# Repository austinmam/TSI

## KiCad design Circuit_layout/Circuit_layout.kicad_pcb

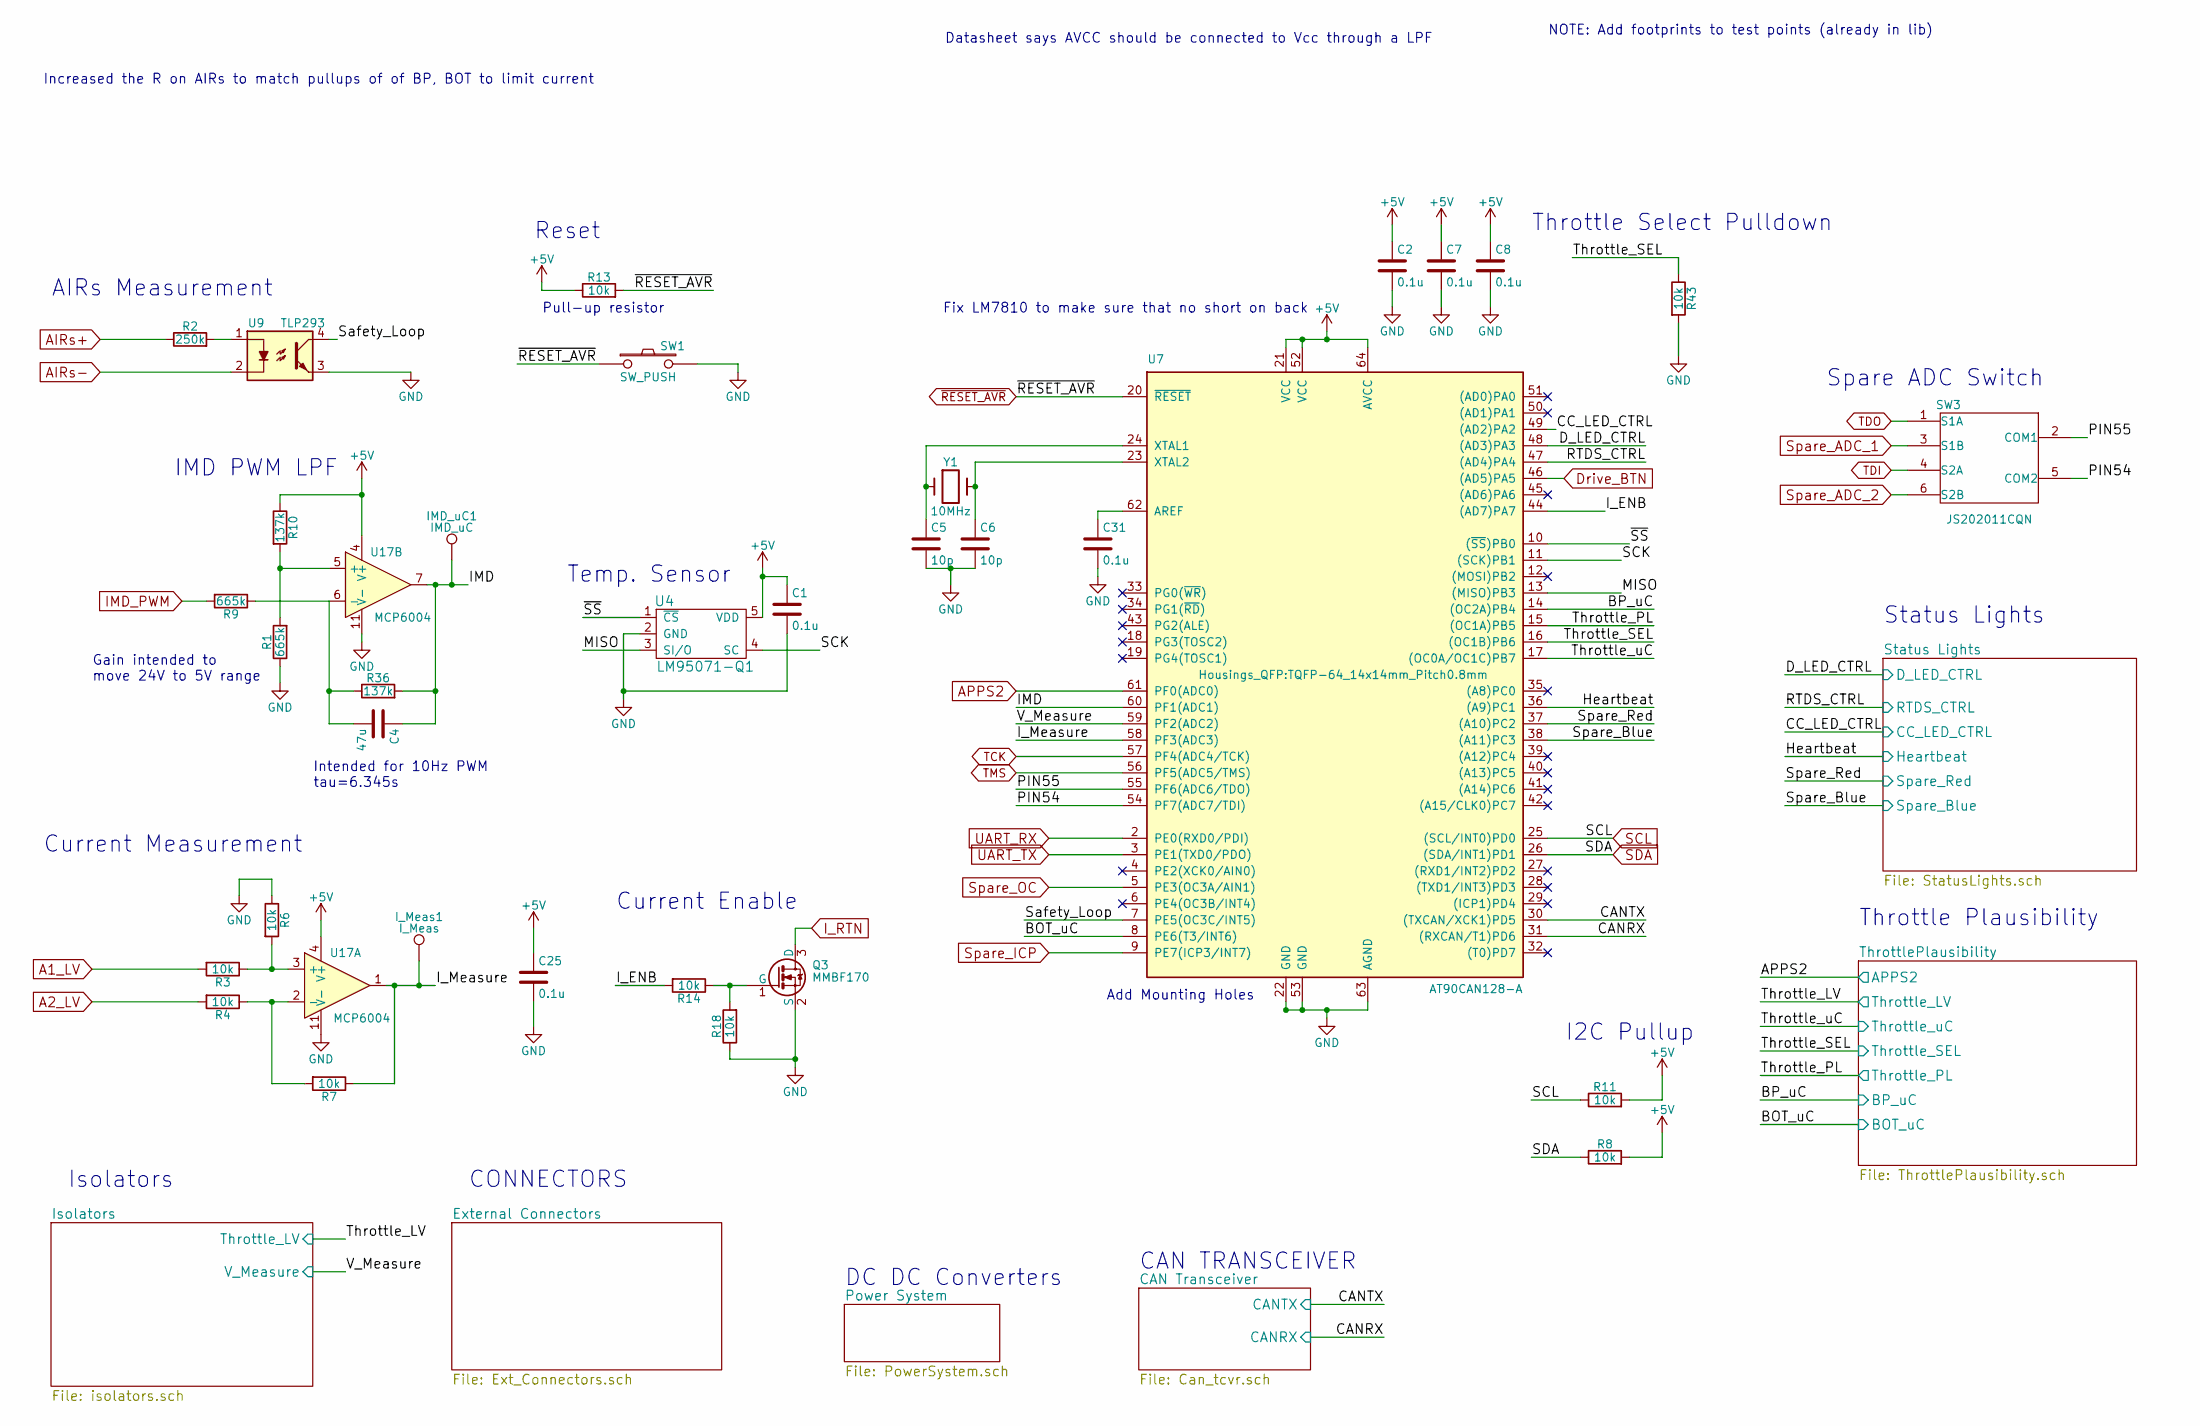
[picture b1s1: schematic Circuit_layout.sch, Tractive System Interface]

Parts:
C1, C2, C7, C8, C25, C31: 0.1u; C_0805_HandSoldering; Digikey P/N 399-1168-1-ND
C4: 47u; C_1210_HandSoldering; Digikey P/N 490-6538-1-ND
C5, C6: 10p; C_0805_HandSoldering; DigiKey P/N 399-1108-1-ND
IMD_uC1: IMD_uC; Measurement_Point_Round-SMD-Pad_Big
I_Meas1: I_Meas; Measurement_Point_Round-SMD-Pad_Big
Q3: MMBF170; SOT-23; Digikey P/N MMBF170CT-ND
R1, R9: 665k; R_0805_HandSoldering; DigiKey P/N P665KCCT-ND
R2: 250k; R_0805_HandSoldering; DigiKey P/N P249KCCT-ND
R3, R4, R6, R7, R8, R11, R13, R14, R18, R43: 10k; R_0805_HandSoldering; DigiKey P/N P10.0KCCT-ND
R10, R36: 137k; R_0805_HandSoldering; DigiKey P/N P137KCCT-ND
SW1: SW_PUSH; SW_RACON_8; DigiKey P/N 1715-1676-1-ND
SW3: JS202011CQN; CK_DPDT_Switch; DigiKey P/N 401-2001-ND
U4: LM95071-Q1; SOT-23-5_HandSoldering; DigiKey P/N 296-40259-1-ND
U7: AT90CAN128-A; TQFP-64_14x14mm_Pitch0.8mm; DigiKey P/N AT90CAN128-16AURCT-ND
U9: TLP293; SOP-4_4.4x2.8mm_Pitch1.27mm; DigiKey P/N TLP293(GB-TPLECT-ND
U17: MCP6004; SOIC-14_3.9x8.7mm_Pitch1.27mm; Digikey P/N MCP6004T-I/SLCT-ND
Y1: 10MHz; crystal_TXC_7A; DigiKey P/N 887-1741-1-ND

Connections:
+5V: C1.1, C2.1, C7.1, C8.1, C25.1, R8.2, R10.1, R11.2, R13.1, U4.5 (VDD), U7.21 (VCC), U7.52 (VCC), U7.64 (AVCC), U17.4 (V+); also elsewhere on the board
/CAN Transceiver/CANRX: U7.31 ((RXCAN/T1)PD6); also elsewhere on the board
/CAN Transceiver/CANTX: U7.30 ((TXCAN/XCK1)PD5); also elsewhere on the board
/IMD: C4.1, IMD_uC1.1, R36.2, U7.60 (PF1(ADC1)), U17.7
/I_ENB: R14.2, U7.44 ((AD7)PA7)
/I_Measure: I_Meas1.1, R7.1, U7.58 (PF3(ADC3)), U17.1
/Isolators/V_Measure: U7.59 (PF2(ADC2)); also elsewhere on the board
/MISO: U4.3 (SI/O), U7.13 ((MISO)PB3)
/PIN54: SW3.5 (COM2), U7.54 (PF7(ADC7/TDI))
/PIN55: SW3.2 (COM1), U7.55 (PF6(ADC6/TDO))
/SCK: U4.4 (SC), U7.11 ((SCK)PB1)
/Safety_Loop: U7.7 (PE5(OC3C/INT5)), U9.4
/Status Lights/CC_LED_CTRL: U7.49 ((AD2)PA2); also elsewhere on the board
/Status Lights/D_LED_CTRL: U7.48 ((AD3)PA3); also elsewhere on the board
/Status Lights/Heartbeat: U7.36 ((A9)PC1); also elsewhere on the board
/Status Lights/RTDS_CTRL: U7.47 ((AD4)PA4); also elsewhere on the board
/Status Lights/Spare_Blue: U7.38 ((A11)PC3); also elsewhere on the board
/Status Lights/Spare_Red: U7.37 ((A10)PC2); also elsewhere on the board
/ThrottlePlausibility/BOT_uC: U7.8 (PE6(T3/INT6)); also elsewhere on the board
/ThrottlePlausibility/BP_uC: U7.14 ((OC2A)PB4); also elsewhere on the board
/ThrottlePlausibility/Throttle_PL: U7.15 ((OC1A)PB5); also elsewhere on the board
/ThrottlePlausibility/Throttle_SEL: R43.1, U7.16 ((OC1B)PB6); also elsewhere on the board
/ThrottlePlausibility/Throttle_uC: U7.17 ((OC0A/OC1C)PB7); also elsewhere on the board
/~SS: U4.1 (~CS), U7.10 ((~SS~)PB0)
A1_LV: R3.2; also elsewhere on the board
A2_LV: R4.2; also elsewhere on the board
AIRs+: R2.1; also elsewhere on the board
AIRs-: U9.2; also elsewhere on the board
APPS2: U7.61 (PF0(ADC0)); also elsewhere on the board
Drive_BTN: U7.46 ((AD5)PA5); also elsewhere on the board
IMD_PWM: R9.2; also elsewhere on the board
I_RTN: Q3.3 (D); also elsewhere on the board
unnamed: C4.2, R9.1, R36.1, U17.6 (-)
unnamed: C5.1, U7.24 (XTAL1), Y1.1
unnamed: C6.1, U7.23 (XTAL2), Y1.2
unnamed: C31.1, U7.62 (AREF)
unnamed: Q3.1 (G), R14.1, R18.2
unnamed: R1.2, R10.2, U17.5 (+)
unnamed: R2.2, U9.1
unnamed: R3.1, R6.2, U17.3 (+)
unnamed: R4.1, R7.2, U17.2 (-)
SCL: R11.1, U7.25 ((SCL/INT0)PD0); also elsewhere on the board
SDA: R8.1, U7.26 ((SDA/INT1)PD1); also elsewhere on the board
Spare_ADC_1: SW3.3 (S1B); also elsewhere on the board
Spare_ADC_2: SW3.6 (S2B); also elsewhere on the board
Spare_ICP: U7.9 (PE7(ICP3/INT7)); also elsewhere on the board
Spare_OC: U7.5 (PE3(OC3A/AIN1)); also elsewhere on the board
TCK: U7.57 (PF4(ADC4/TCK)); also elsewhere on the board
TDI: SW3.4 (S2A); also elsewhere on the board
TDO: SW3.1 (S1A); also elsewhere on the board
TMS: U7.56 (PF5(ADC5/TMS)); also elsewhere on the board
UART_RX: U7.2 (PE0(RXD0/PDI)); also elsewhere on the board
UART_TX: U7.3 (PE1(TXD0/PDO)); also elsewhere on the board
~RESET_AVR: R13.2, SW1.1, U7.20 (~RESET); also elsewhere on the board

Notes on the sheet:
CONNECTORS
CAN TRANSCEIVER
Current Measurement
IMD PWM LPF
AIRs Measurement
Throttle Plausibility
Status Lights
DC DC Converters
Isolators
Add Mounting Holes
Intended for 10Hz PWM tau=6.345s
I2C Pullup
Datasheet says AVCC should be connected to Vcc through a LPF
Pull-up resistor
Reset
Throttle Select Pulldown
NOTE: Add footprints to test points (already in lib)
Spare ADC Switch
Increased the R on AIRs to match pullups of of BP, BOT to limit current
Current Enable
Gain intended to move 24V to 5V range
Temp. Sensor
Fix LM7810 to make sure that no short on back

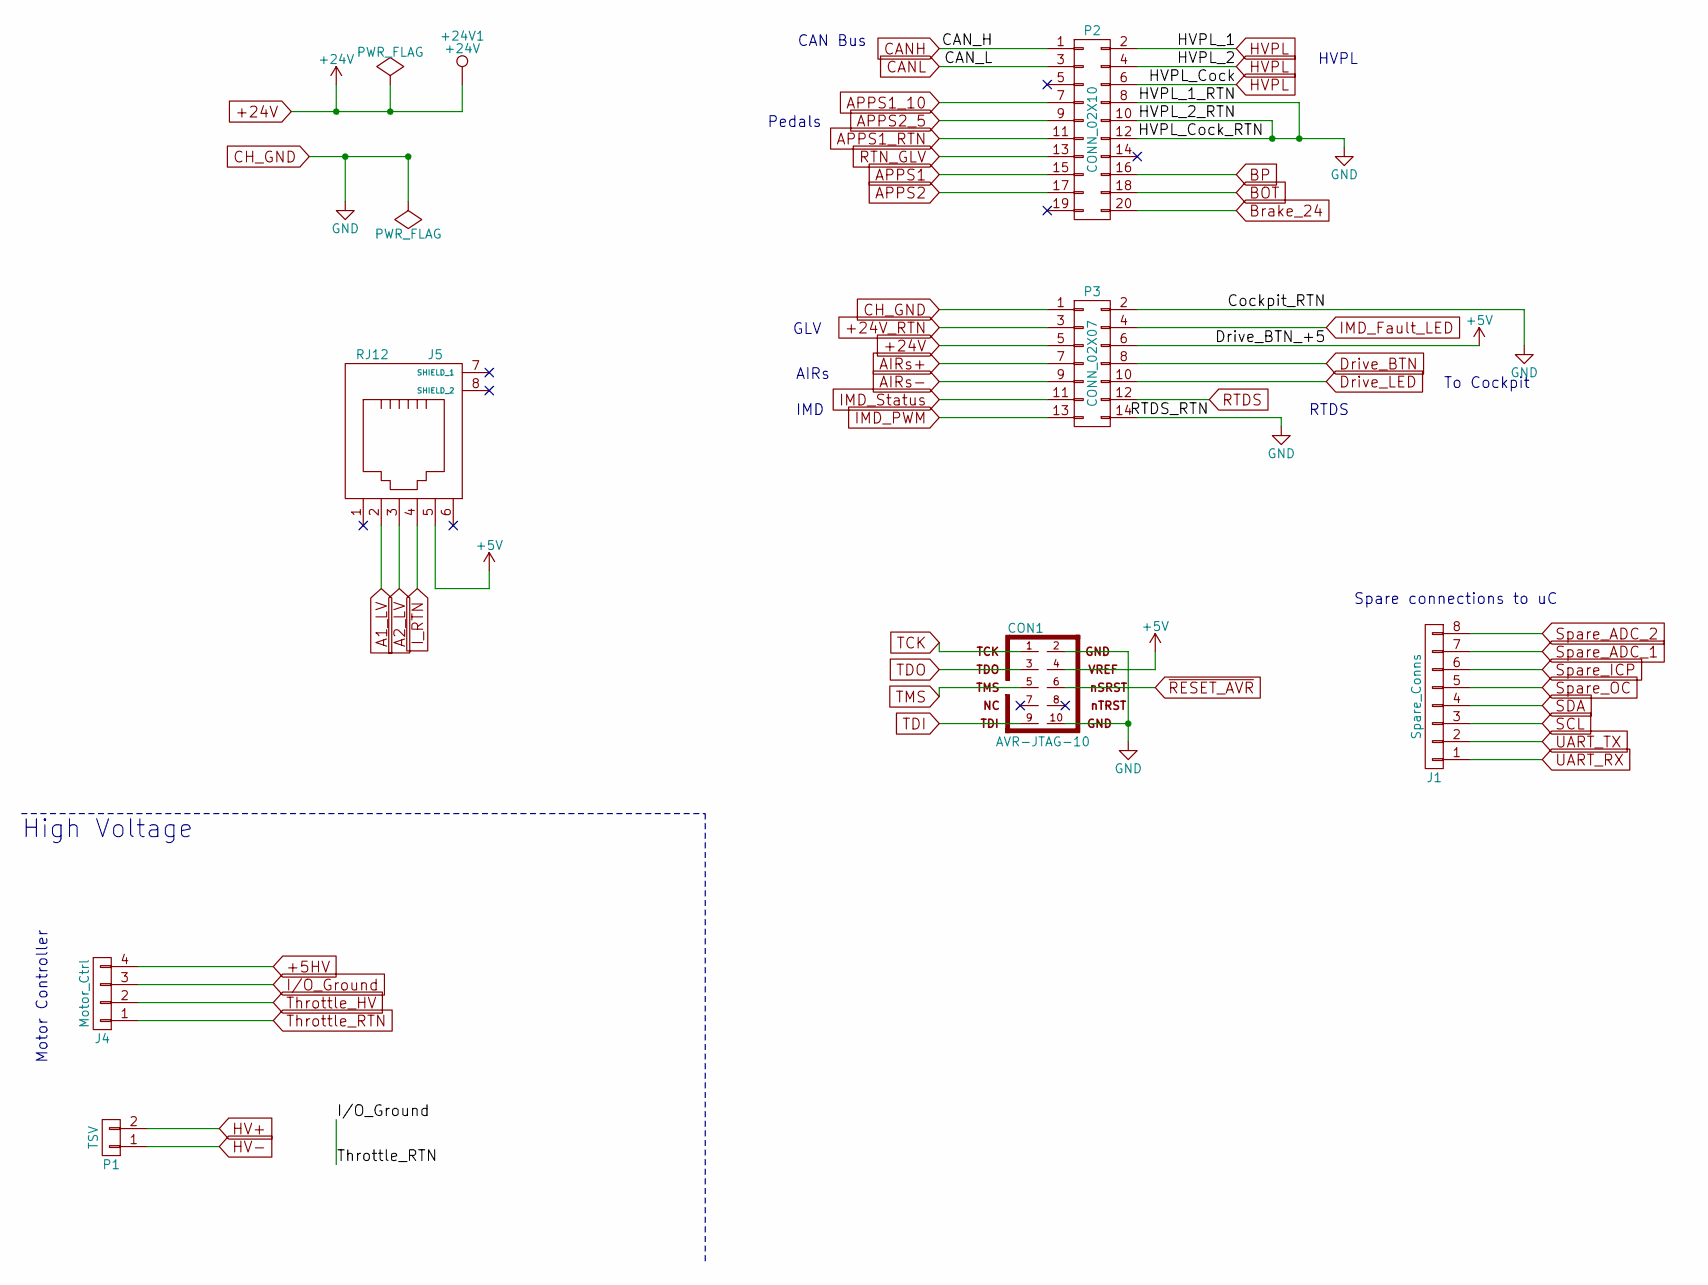
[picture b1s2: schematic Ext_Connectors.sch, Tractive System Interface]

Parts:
+24V1: +24V; Measurement_Point_Round-SMD-Pad_Big
CON1: AVR-JTAG-10; JTAG; DigiKey P/N 609-4054-ND
J1: Spare_Conns; Molex_8x1_2.54mm; DigiKey P/N WM4128-ND
J4: Motor_Ctrl; Molex_4x1_2.54mm; DigiKey P/N WM4802-ND
J5: RJ12; MOLEX_RJ11; DigiKey P/N WM3789CT-ND
P1: TSV; AMPCONN_2; DigiKey P/N A113980-ND
P2: CONN_02X10; IDC_Header_Straight_20pins; DigiKey P/N WM14741-ND
P3: CONN_02X07; IDC_Header_Straight_14pins; DigiKey P/N WM8632-ND

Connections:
+5HV: J4.4; also elsewhere on the board
+5V: CON1.4, J5.5, P3.6; also elsewhere on the board
+24V: +24V1.1, P2.20, P3.5; also elsewhere on the board
+24V_RTN: P3.3; also elsewhere on the board
A1_LV: J5.2; also elsewhere on the board
A2_LV: J5.3; also elsewhere on the board
AIRs+: P3.7; also elsewhere on the board
AIRs-: P3.9; also elsewhere on the board
APPS1: P2.15; also elsewhere on the board
APPS1_10: P2.7; also elsewhere on the board
APPS1_RTN: P2.11; also elsewhere on the board
APPS2: P2.17; also elsewhere on the board
APPS2_5: P2.9; also elsewhere on the board
BOT: P2.18; also elsewhere on the board
BP: P2.16; also elsewhere on the board
CANH: P2.1; also elsewhere on the board
CANL: P2.3; also elsewhere on the board
Drive_BTN: P3.8; also elsewhere on the board
Drive_LED: P3.10; also elsewhere on the board
HV+: P1.2; also elsewhere on the board
HV-: P1.1; also elsewhere on the board
HVPL: P2.2, P2.4, P2.6; also elsewhere on the board
I/O_Ground: J4.1, J4.3; also elsewhere on the board
IMD_Fault_LED: P3.4; also elsewhere on the board
IMD_PWM: P3.13; also elsewhere on the board
IMD_Status: P3.11; also elsewhere on the board
I_RTN: J5.4; also elsewhere on the board
RTDS: P3.12; also elsewhere on the board
SCL: J1.3; also elsewhere on the board
SDA: J1.4; also elsewhere on the board
Spare_ADC_1: J1.7; also elsewhere on the board
Spare_ADC_2: J1.8; also elsewhere on the board
Spare_ICP: J1.6; also elsewhere on the board
Spare_OC: J1.5; also elsewhere on the board
TCK: CON1.1; also elsewhere on the board
TDI: CON1.9; also elsewhere on the board
TDO: CON1.3; also elsewhere on the board
TMS: CON1.5; also elsewhere on the board
Throttle_HV: J4.2; also elsewhere on the board
UART_RX: J1.1; also elsewhere on the board
UART_TX: J1.2; also elsewhere on the board
~RESET_AVR: CON1.6; also elsewhere on the board

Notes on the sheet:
To Cockpit
Motor Controller
AIRs
CAN Bus
High Voltage
IMD
GLV
Spare connections to uC
RTDS
Pedals
HVPL

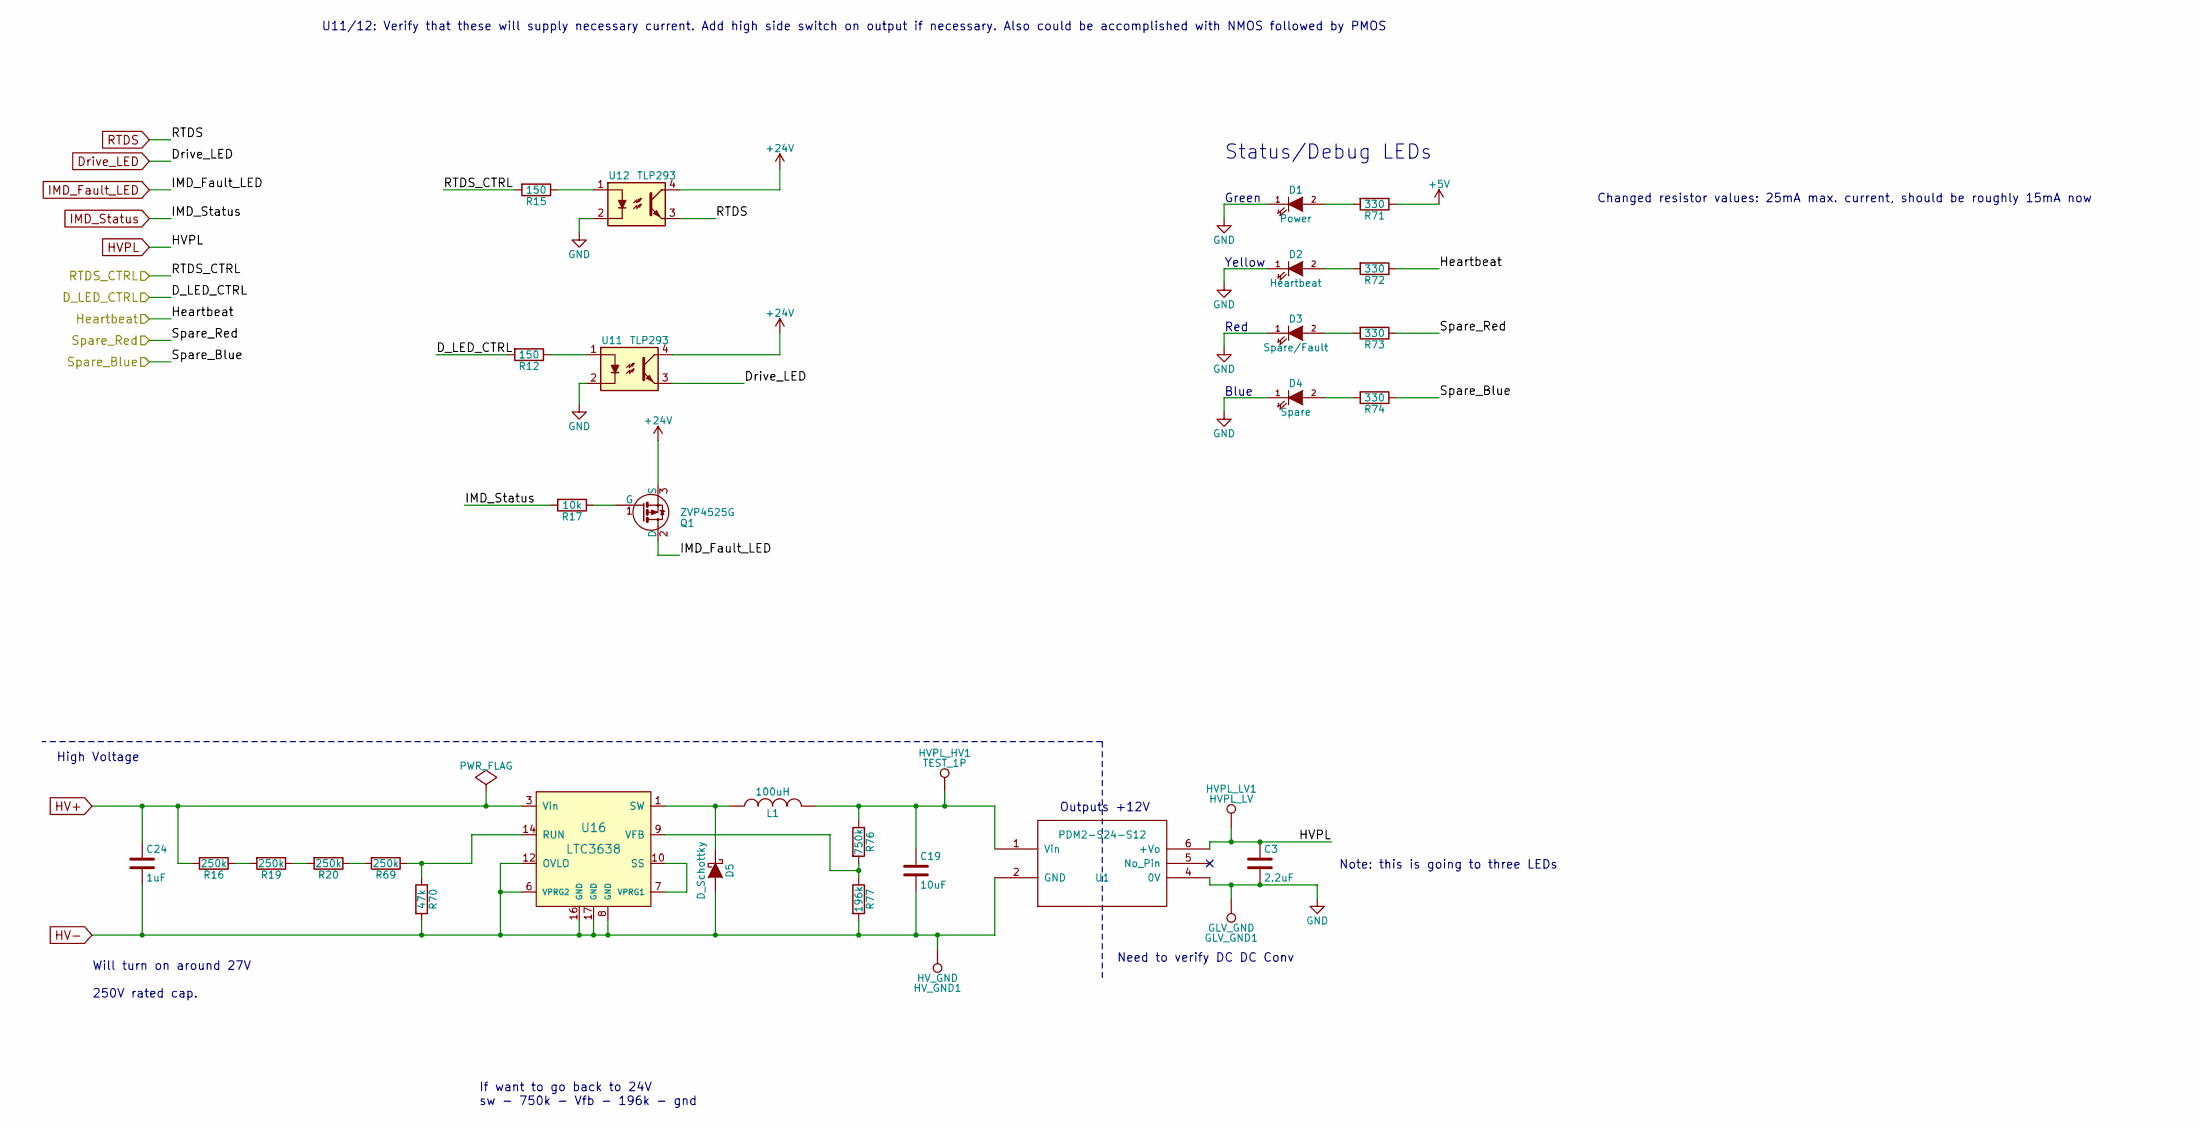
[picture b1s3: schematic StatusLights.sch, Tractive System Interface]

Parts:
C3: 2.2uF; C_0805_HandSoldering; DigiKey P/N 587-1293-1-ND
C19: 10uF; C_0805_HandSoldering; DigiKey P/N 490-10515-1-ND
C24: 1uF; C_2220_HandSoldering; DigiKey P/N 490-3550-1-ND
D1: Power; LED_0805; DigiKey P/N 475-1410-1-ND
D2: Heartbeat; LED_0805; DigiKey P/N 475-2560-1-ND
D3: Spare/Fault; LED_0805; DigiKey P/N 475-1278-1-ND
D4: Spare; LED_0805; DigiKey P/N 516-1445-1-ND
D5: D_Schottky; do214ac; DigiKey P/N SK310A-LTPMSCT-ND
GLV_GND1: GLV_GND; Measurement_Point_Square-SMD-Pad_Big
HVPL_HV1: TEST_1P; Measurement_Point_Round-SMD-Pad_Big
HVPL_LV1: HVPL_LV; Measurement_Point_Round-SMD-Pad_Big
HV_GND1: HV_GND; Measurement_Point_Square-SMD-Pad_Big
L1: 100uH; Inductor_Taiyo-Yuden_NR-80xx_HandSoldering; DigiKey P/N 587-2004-1-ND
Q1: ZVP4525G; SOT-223-3Lead_TabPin2; DigiKey P/N ZVP4525GCT-ND
R12, R15: 150; R_0805_HandSoldering; DigiKey P/N 311-150CRCT-ND
R16, R19, R20, R69: 250k; R_0805_HandSoldering; DigiKey P/N P249KCCT-ND
R17: 10k; R_0805_HandSoldering; DigiKey P/N P10.0KCCT-ND
R70: 47k; R_0805_HandSoldering; DigiKey P/N 311-47.0KCRCT-ND
R71, R72, R73, R74: 330; R_0805_HandSoldering; DigiKey P/N P330CCT-ND
R76: 750k; R_0805_HandSoldering; DigiKey P/N P750KCCT-ND
R77: 196k; R_0805_HandSoldering; DigiKey P/N P196CCT-ND
U1: PDM2-S24-S12; DCDC-Conv_TRACO_TMR_1-xxxx_Single; DigiKey P/N 102-2728-ND
U11, U12: TLP293; SOP-4_4.4x2.8mm_Pitch1.27mm; DigiKey P/N TLP293(GB-TPLECT-ND
U16: LTC3638; TSSOP16_LTC3638; DigiKey P/N LTC3638EMSE#PBF-ND

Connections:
+5V: R71.1; also elsewhere on the board
+24V: Q1.3 (S), U11.4, U12.4; also elsewhere on the board
/Status Lights/D_LED_CTRL: R12.2; also elsewhere on the board
/Status Lights/Heartbeat: R72.1; also elsewhere on the board
/Status Lights/RTDS_CTRL: R15.2; also elsewhere on the board
/Status Lights/Spare_Blue: R74.1; also elsewhere on the board
/Status Lights/Spare_Red: R73.1; also elsewhere on the board
Drive_LED: U11.3; also elsewhere on the board
HV+: C24.1, R16.2, U16.3 (Vin); also elsewhere on the board
HV-: C19.2, C24.2, D5.2 (A), HV_GND1.1, R70.2, R77.2, U1.2 (GND), U16.6 (VPRG2), U16.8 (GND), U16.12 (OVLO), U16.16 (GND), U16.17 (GND); also elsewhere on the board
HVPL: C3.1, HVPL_LV1.1, U1.6 (+Vo); also elsewhere on the board
IMD_Fault_LED: Q1.2 (D); also elsewhere on the board
IMD_Status: R17.2; also elsewhere on the board
unnamed: C19.1, HVPL_HV1.1, L1.2, R76.1, U1.1 (Vin)
unnamed: D1.2 (A), R71.2
unnamed: D2.2 (A), R72.2
unnamed: D3.2 (A), R73.2
unnamed: D4.2 (A), R74.2
unnamed: D5.1 (K), L1.1, U16.1 (SW)
unnamed: Q1.1 (G), R17.1
unnamed: R12.1, U11.1
unnamed: R15.1, U12.1
unnamed: R16.1, R19.2
unnamed: R19.1, R20.2
unnamed: R20.1, R69.2
unnamed: R69.1, R70.1, U16.14 (RUN)
unnamed: R76.2, R77.1, U16.9 (VFB)
unnamed: U16.7 (VPRG1), U16.10 (SS)
RTDS: U12.3; also elsewhere on the board

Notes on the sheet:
Green
Yellow
Red
Blue
Status/Debug LEDs
High Voltage
If want to go back to 24V sw - 750k - Vfb - 196k - gnd
Will turn on around 27V 250V rated cap.
Changed resistor values: 25mA max. current, should be roughly 15mA now
Note: this is going to three LEDs
Need to verify DC DC Conv
Outputs +12V
U11/12: Verify that these will supply necessary current. Add high side switch on output if necessary. Also could be accomplished with NMOS followed by PMOS

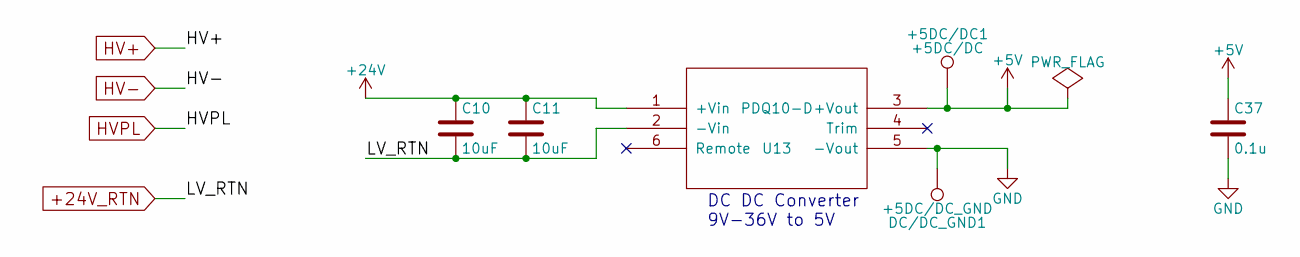
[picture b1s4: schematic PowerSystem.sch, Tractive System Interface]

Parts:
+5DC/DC1: +5DC/DC; Measurement_Point_Round-SMD-Pad_Big
C10, C11: 10uF; C_0805_HandSoldering; DigiKey P/N 490-10515-1-ND
C37: 0.1u; C_0805_HandSoldering; Digikey P/N 399-1168-1-ND
DC/DC_GND1: +5DC/DC_GND; Measurement_Point_Square-SMD-Pad_Big
U13: PDQ10-D; PDQ_DCDC; DigiKey P/N 102-3865-ND

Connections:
+5V: +5DC/DC1.1, C37.1, U13.3 (+Vout); also elsewhere on the board
+24V: C10.1, C11.1, U13.1 (+Vin); also elsewhere on the board
+24V_RTN: C10.2, C11.2, U13.2 (-Vin); also elsewhere on the board

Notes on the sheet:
DC DC Converter 9V-36V to 5V

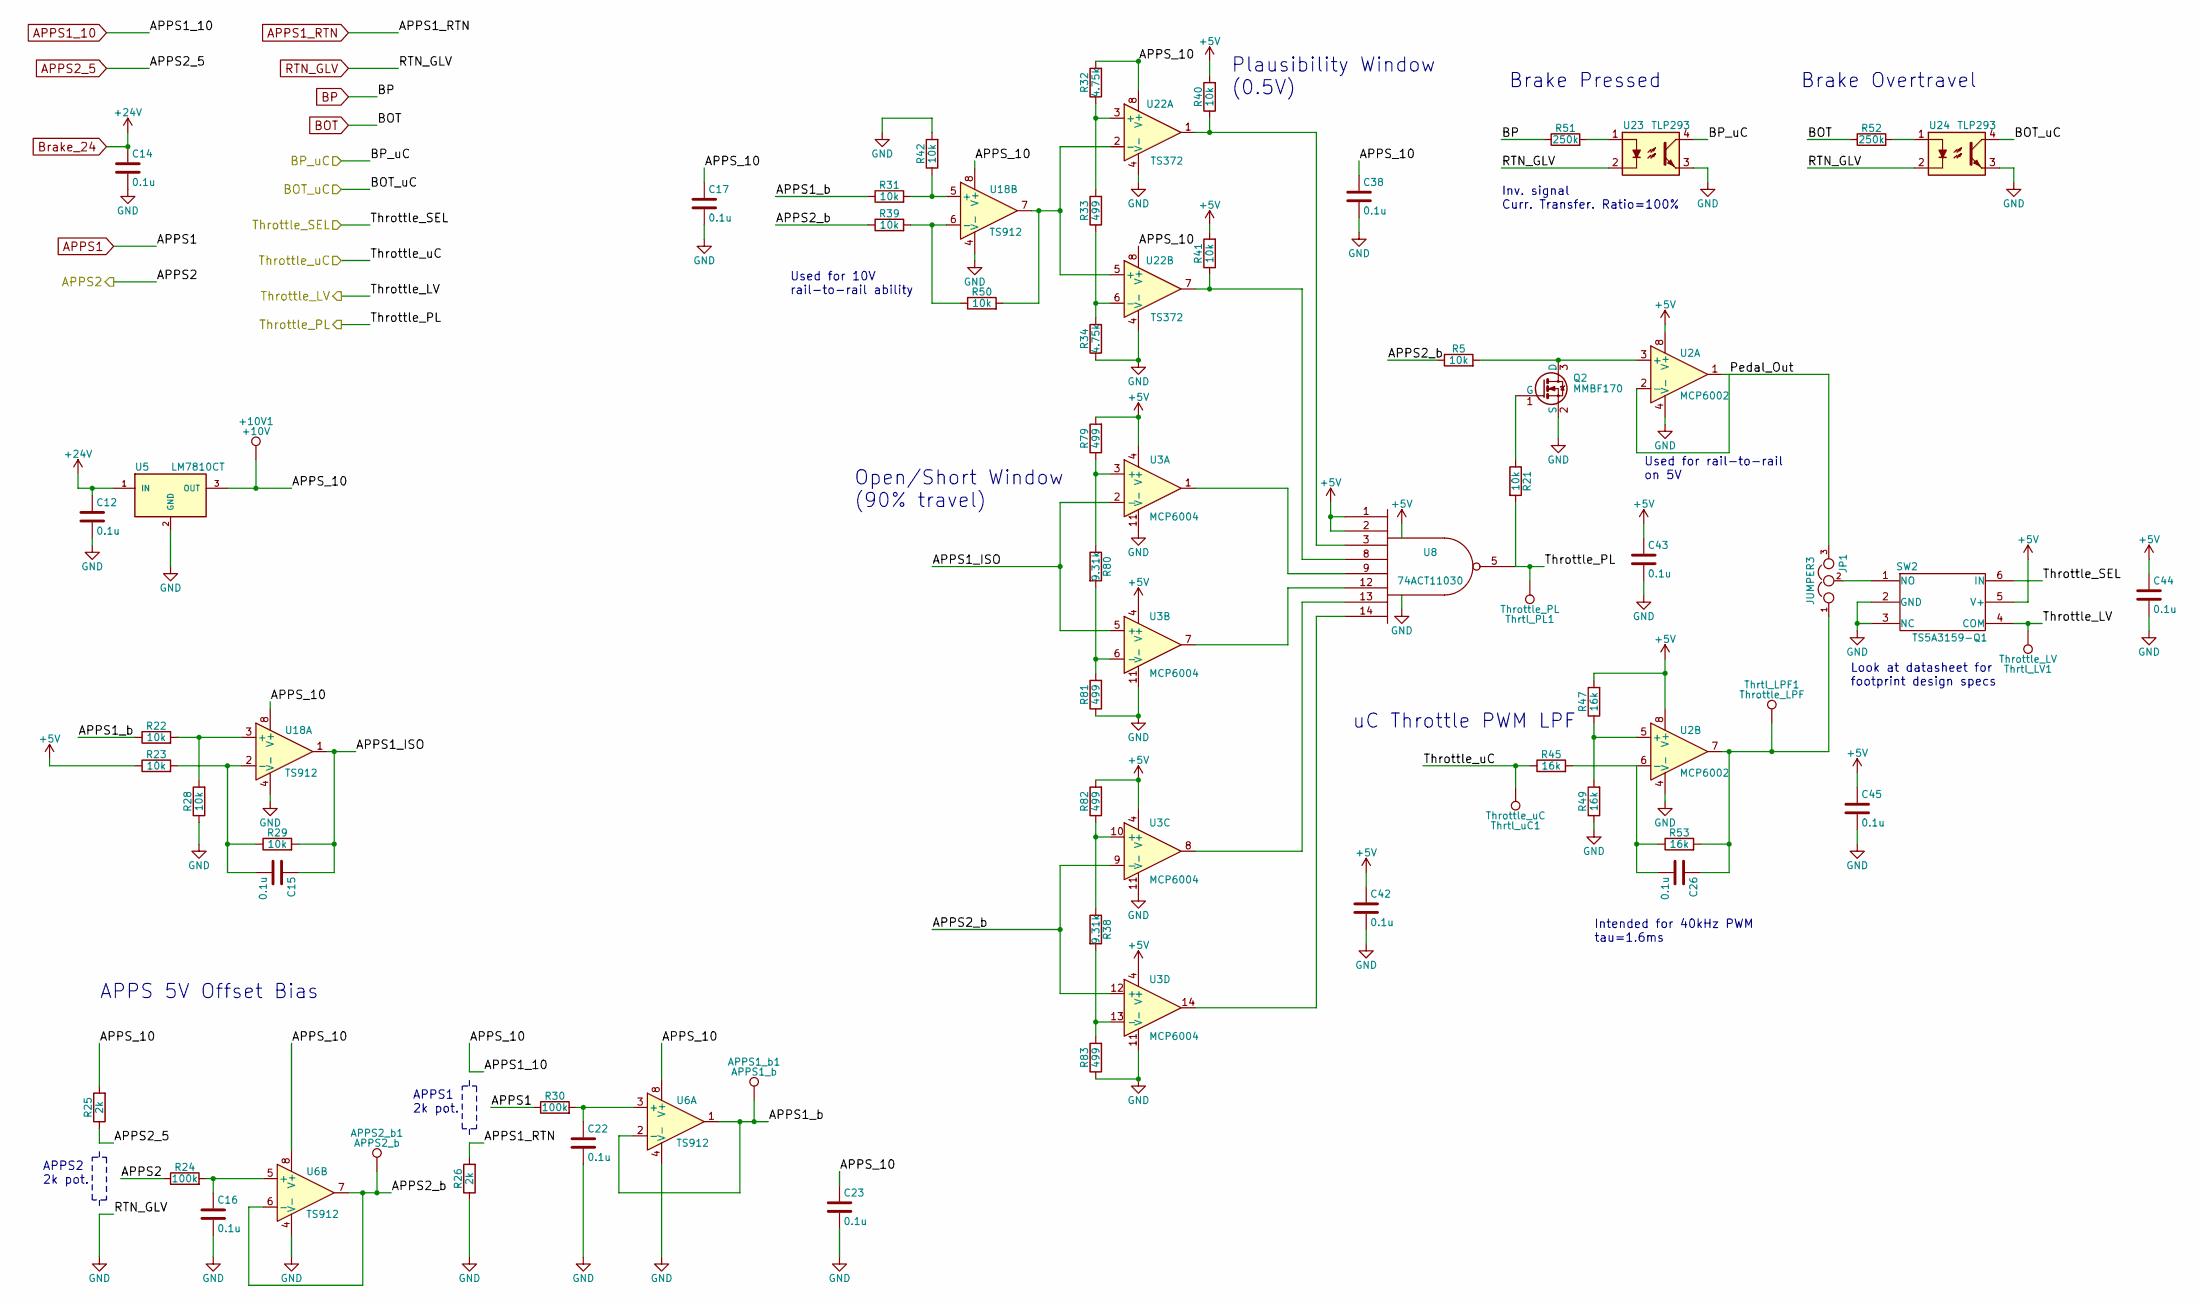
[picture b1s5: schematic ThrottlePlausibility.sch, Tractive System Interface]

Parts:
+10V1: +10V; Measurement_Point_Round-SMD-Pad_Big
APPS1_b1: APPS1_b; Measurement_Point_Round-SMD-Pad_Big
APPS2_b1: APPS2_b; Measurement_Point_Round-SMD-Pad_Big
C12, C14, C15, C16, C17, C22, C23, C26, C38, C42, C43, C44, C45: 0.1u; C_0805_HandSoldering; Digikey P/N 399-1168-1-ND
JP1: JUMPER3; Pin_Header_Straight_1x03_Pitch2.54mm; DigiKey P/N Z5375-ND
Q2: MMBF170; SOT-23; Digikey P/N MMBF170CT-ND
R5, R21, R22, R23, R28, R29, R31, R39, R40, R41, R42, R50: 10k; R_0805_HandSoldering; DigiKey P/N P10.0KCCT-ND
R24, R30: 100k; R_0805_HandSoldering; DigiKey P/N P100KCCT-ND
R25, R26: 2k; R_0805_HandSoldering; DigiKey P/N P2.00KCCT-ND
R32, R34: 4.75k; R_0805_HandSoldering; DigiKey P/N P4.75KCCT-ND
R33, R79, R81, R82, R83: 499; R_0805_HandSoldering; DigiKey P/N P499DACT-ND
R38, R80: 9.31k; R_0805_HandSoldering; Digikey P/N P9.31KCCT-ND
R45, R47, R49, R53: 16k; R_0805_HandSoldering; DigiKey P/N P16KACT-ND
R51, R52: 250k; R_0805_HandSoldering; DigiKey P/N P249KCCT-ND
SW2: TS5A3159-Q1; SOT-23-6_Handsoldering; DigiKey P/N 296-39512-1-ND
Thrtl_LPF1: Throttle_LPF; Measurement_Point_Round-SMD-Pad_Big
Thrtl_LV1: Throttle_LV; Measurement_Point_Round-SMD-Pad_Big
Thrtl_PL1: Throttle_PL; Measurement_Point_Round-SMD-Pad_Big
Thrtl_uC1: Throttle_uC; Measurement_Point_Round-SMD-Pad_Big
U2: MCP6002; SOIC-8_3.9x4.9mm_Pitch1.27mm; DigiKey P/N MCP6002T-I/SNCT-ND
U3: MCP6004; SOIC-14_3.9x8.7mm_Pitch1.27mm; Digikey P/N MCP6004T-I/SLCT-ND
U5: LM7810CT; TO-220_Horizontal; DigiKey P/N LM7810CT-ND
U6, U18: TS912; SOIC-8_3.9x4.9mm_Pitch1.27mm; DigiKey P/N 497-10252-1-ND
U8: 74ACT11030; SOIC-14_3.9x8.7mm_Pitch1.27mm; Digikey P/N 296-4180-1-ND
U22: TS372; SOIC-8_3.9x4.9mm_Pitch1.27mm; DigiKey P/N 497-2271-1-ND
U23, U24: TLP293; SOP-4_4.4x2.8mm_Pitch1.27mm; DigiKey P/N TLP293(GB-TPLECT-ND

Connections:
+5V: C42.1, C43.1, C44.1, C45.1, R23.1, R40.2, R41.2, R47.2, R79.2, R82.2, SW2.5 (V+), U2.8 (V+), U3.4 (V+), U8.1, U8.2, U8.11 (VCC); also elsewhere on the board
+24V: C12.1, C14.1, U5.1 (IN); also elsewhere on the board
/Isolators/Throttle_LV: SW2.4 (COM), Thrtl_LV1.1; also elsewhere on the board
/ThrottlePlausibility/APPS1_ISO: C15.1, R29.2, U3.2 (-), U3.5 (+), U18.1
/ThrottlePlausibility/APPS1_b: APPS1_b1.1, R22.1, R31.1, U6.1, U6.2 (-)
/ThrottlePlausibility/APPS2_b: APPS2_b1.1, R5.1, R39.1, U3.9 (-), U3.12 (+), U6.6 (-), U6.7
/ThrottlePlausibility/BOT_uC: U24.4; also elsewhere on the board
/ThrottlePlausibility/BP_uC: U23.4; also elsewhere on the board
/ThrottlePlausibility/Pedal_Out: JP1.3, U2.1, U2.2 (-)
/ThrottlePlausibility/Throttle_PL: R21.2, Thrtl_PL1.1, U8.5; also elsewhere on the board
/ThrottlePlausibility/Throttle_SEL: SW2.6 (IN); also elsewhere on the board
/ThrottlePlausibility/Throttle_uC: R45.1, Thrtl_uC1.1; also elsewhere on the board
APPS1: R30.1; also elsewhere on the board
APPS1_10: +10V1.1, C17.1, C23.1, C38.1, R25.2, R32.2, U5.3 (OUT), U6.8 (V+), U18.8 (V+), U22.8 (V+); also elsewhere on the board
APPS1_RTN: R26.2; also elsewhere on the board
APPS2: R24.1; also elsewhere on the board
APPS2_5: R25.1; also elsewhere on the board
BOT: R52.1; also elsewhere on the board
BP: R51.1; also elsewhere on the board
unnamed: C15.2, R23.2, R29.1, U18.2 (-)
unnamed: C16.1, R24.2, U6.5 (+)
unnamed: C22.1, R30.2, U6.3 (+)
unnamed: C26.1, JP1.1, R53.2, Thrtl_LPF1.1, U2.7
unnamed: C26.2, R45.2, R53.1, U2.6 (-)
unnamed: JP1.2, SW2.1 (NO)
unnamed: Q2.1 (G), R21.1
unnamed: Q2.3 (D), R5.2, U2.3 (+)
unnamed: R22.2, R28.2, U18.3 (+)
unnamed: R31.2, R42.1, U18.5 (+)
unnamed: R32.1, R33.2, U22.3 (+)
unnamed: R33.1, R34.2, U22.6 (-)
unnamed: R38.1, R82.1, U3.10 (+)
unnamed: R38.2, R83.2, U3.13 (-)
unnamed: R39.2, R50.1, U18.6 (-)
unnamed: R40.1, U8.3, U22.1
unnamed: R41.1, U8.8, U22.7
unnamed: R47.1, R49.2, U2.5 (+)
unnamed: R50.2, U18.7, U22.2 (-), U22.5 (+)
unnamed: R51.2, U23.1
unnamed: R52.2, U24.1
unnamed: R79.1, R80.1, U3.3 (+)
unnamed: R80.2, R81.2, U3.6 (-)
unnamed: U3.1, U8.9
unnamed: U3.7, U8.12
unnamed: U3.8, U8.13
unnamed: U3.14, U8.14

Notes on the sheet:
Used for 10V rail-to-rail ability
Used for rail-to-rail on 5V
Intended for 40kHz PWM tau=1.6ms
Plausibility Window (0.5V)
uC Throttle PWM LPF
Brake Pressed
Open/Short Window (90% travel)
APPS2 2k pot.
APPS1 2k pot.
Brake Overtravel
Inv. signal Curr. Transfer. Ratio=100%
APPS 5V Offset Bias
Look at datasheet for footprint design specs
